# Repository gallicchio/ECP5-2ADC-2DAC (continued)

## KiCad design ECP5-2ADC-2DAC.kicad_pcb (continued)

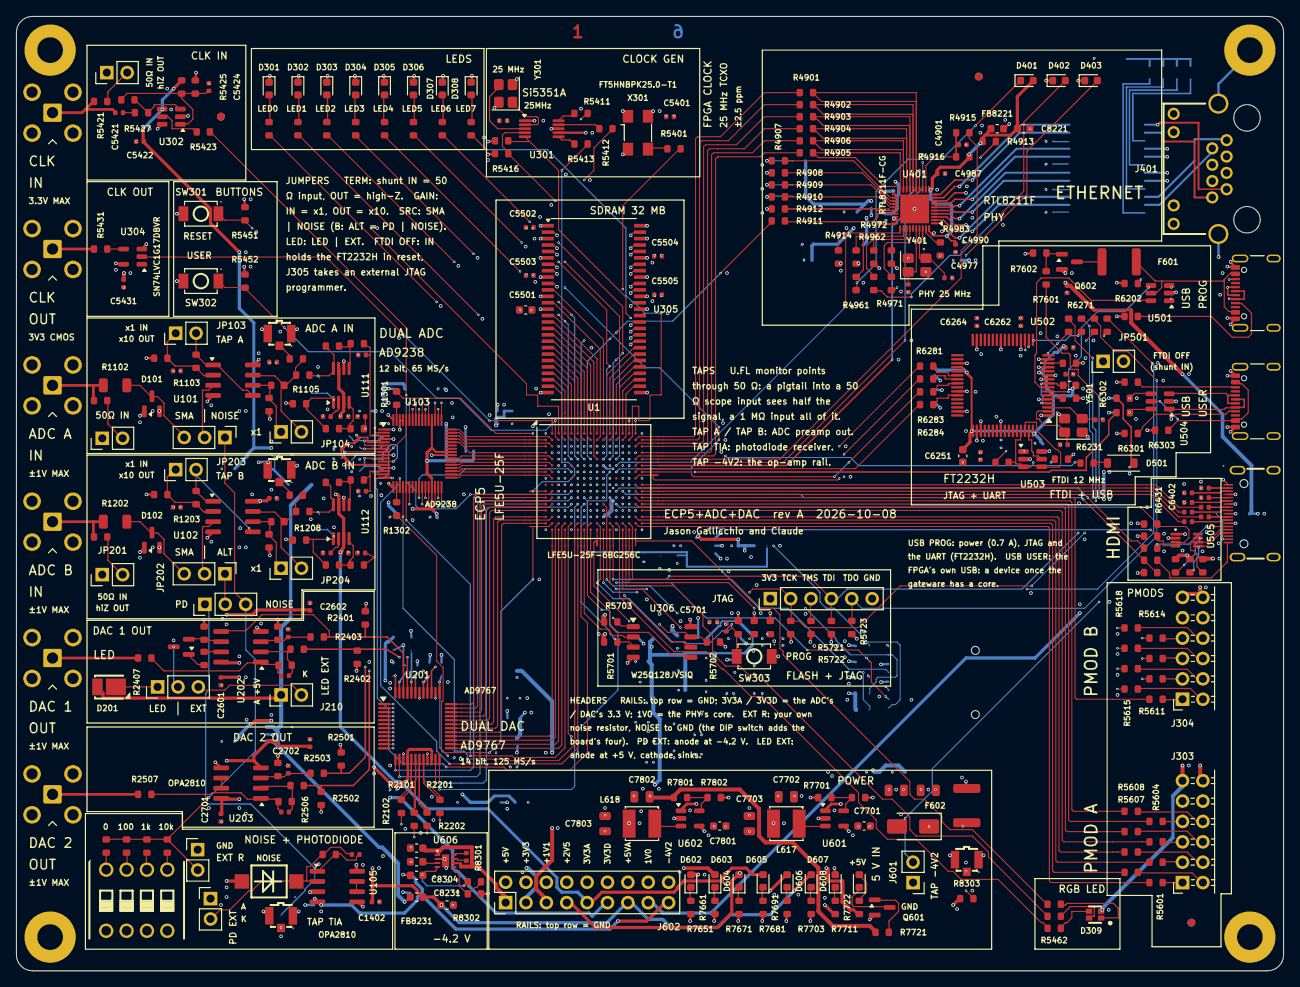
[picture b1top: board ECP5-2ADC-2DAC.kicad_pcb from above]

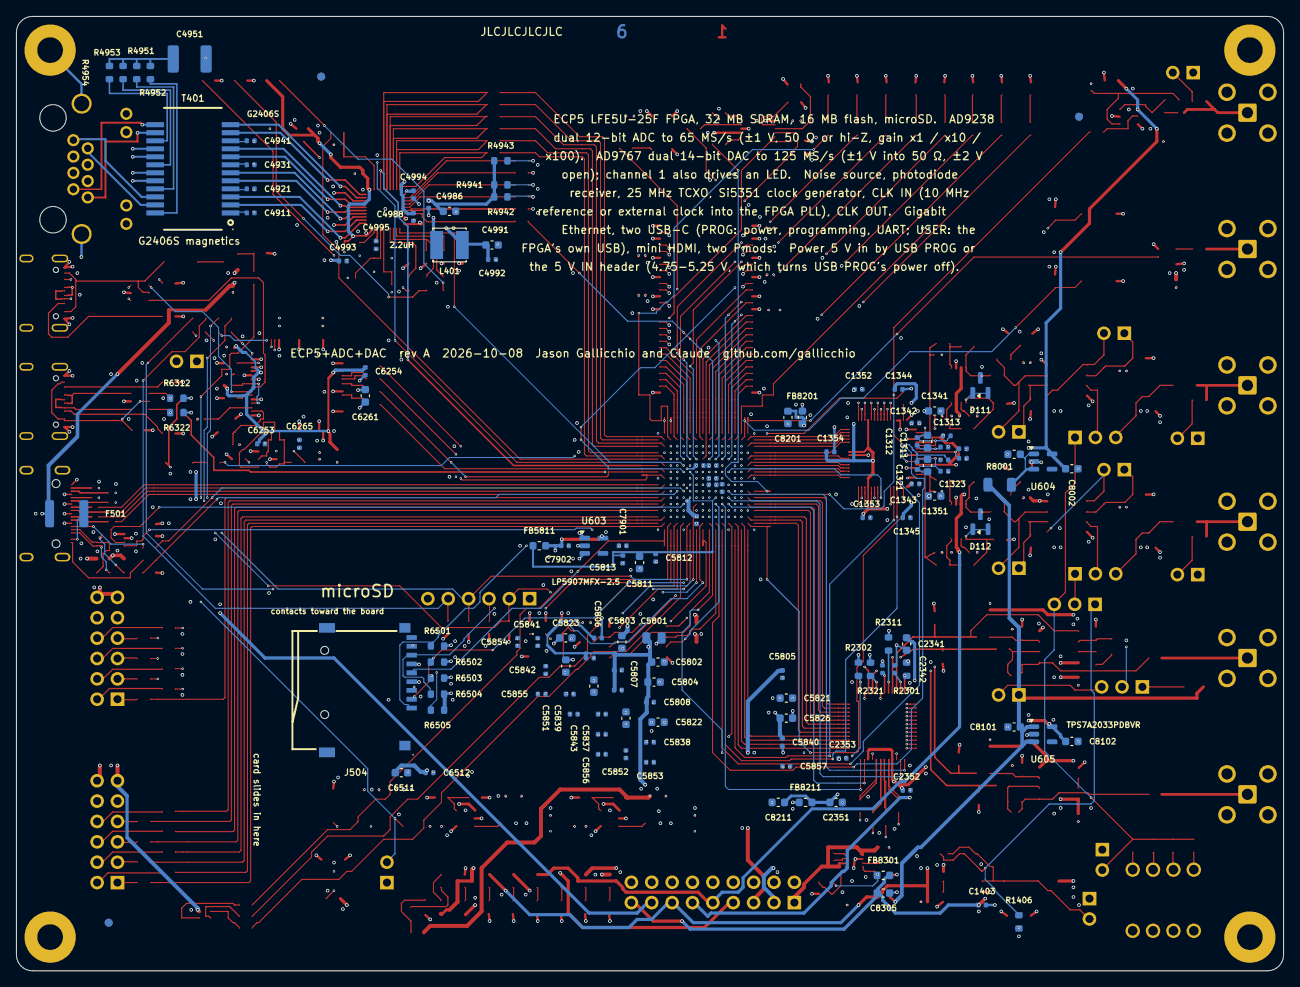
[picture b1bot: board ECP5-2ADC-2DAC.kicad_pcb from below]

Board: 6 copper layers, 158.0 x 119.0 mm, 478 parts (127 on the bottom side), 446 nets.

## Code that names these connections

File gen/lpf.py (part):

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         '_io = [',
         '    # Clocks: 25 MHz TCXO is the default; the Si5351 outputs and the external SMA are also PCLK inputs',
         '    ("clk25",   0, Pins("%s"), IOStandard("LVCMOS33")),' % a["CLK_TCXO"],
         '    ("clk_ext", 0, Pins("%s"), IOStandard("LVCMOS33")),' % a["CLK_EXT"],
         '    ("clk_si",  0, Pins("%s"), IOStandard("LVCMOS33")),' % a["CLK_SI0"],
         '    ("clk_si",  1, Pins("%s"), IOStandard("LVCMOS33")),' % a["CLK_SI1"],
         '    ("clk_si",  2, Pins("%s"), IOStandard("LVCMOS33")),' % a["CLK_SI2"],
         '    ("clk_out", 0, Pins("%s"), IOStandard("LVCMOS33")),' % a["CLK_OUT"],
         '    ("rst",     0, Pins("%s"), IOStandard("LVCMOS33"), Misc("PULLMODE=UP")),' % a["BTN0"],
         '    ("user_btn", 0, Pins("%s"), IOStandard("LVCMOS33"), Misc("PULLMODE=UP")),' % a["BTN0"],
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        L.append('    ("user_led", %d, Pins("%s"), IOStandard("LVCMOS33")),' % (i, a["LED%d" % i]))
    L += ['    # Serial: FT2232H channel B',
          '    ("serial", 0,',
          '        Subsignal("tx", Pins("%s")),' % a["UART_TX"],
          '        Subsignal("rx", Pins("%s")),' % a["UART_RX"],
          '        IOStandard("LVCMOS33")',
          '    ),',
          '    # SDR SDRAM: W9825G6KH-6, 32 MB',
          '    ("sdram_clock", 0, Pins("%s"), IOStandard("LVCMOS33")),' % a["SDRAM_CLK"],
          '    ("sdram", 0,',
          '        Subsignal("a",     Pins("%s")),' % P(["SDRAM_A%d" % i for i in range(13)]),
          '        Subsignal("dq",    Pins("%s")),' % P(["SDRAM_DQ%d" % i for i in range(16)]),
          '        Subsignal("we_n",  Pins("%s")),' % a["SDRAM_WE_N"],
          '        Subsignal("ras_n", Pins("%s")),' % a["SDRAM_RAS_N"],
          '        Subsignal("cas_n", Pins("%s")),' % a["SDRAM_CAS_N"],
          '        Subsignal("cs_n",  Pins("%s")),' % a["SDRAM_CS_N"],
          '        Subsignal("cke",   Pins("%s")),' % a["SDRAM_CKE"],
          '        Subsignal("ba",    Pins("%s")),' % P(["SDRAM_BA0", "SDRAM_BA1"]),
          '        Subsignal("dm",    Pins("%s")),' % P(["SDRAM_DQML", "SDRAM_DQMH"]),
          '        IOStandard("LVCMOS33"), Misc("SLEWRATE=SLOW"),      # unterminated 8-31 mm lines at 100 MHz: slow edges are the termination',
          '    ),',
          '    # SPI flash: W25Q128JVS on the sysCONFIG pins (CLK = CCLK, driven through USRMCLK)',
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          '    ),',
          '    # microSD',
          '    ("spisdcard", 0,',
          '        Subsignal("clk",  Pins("%s")),' % a["SD_CLK"],
          '        Subsignal("mosi", Pins("%s"), Misc("PULLMODE=UP")),' % a["SD_CMD"],
          '        Subsignal("cs_n", Pins("%s"), Misc("PULLMODE=UP")),' % a["SD_D3"],
          '        Subsignal("miso", Pins("%s"), Misc("PULLMODE=UP")),' % a["SD_D0"],
          '        Misc("SLEWRATE=FAST"), IOStandard("LVCMOS33"),',
          '    ),',
          '    ("sdcard", 0,',
          '        Subsignal("clk",  Pins("%s")),' % a["SD_CLK"],
          '        Subsignal("cmd",  Pins("%s"), Misc("PULLMODE=UP")),' % a["SD_CMD"],
          '        Subsignal("data", Pins("%s"), Misc("PULLMODE=UP")),' % P(["SD_D0", "SD_D1", "SD_D2", "SD_D3"]),
          '        Misc("SLEWRATE=FAST"), IOStandard("LVCMOS33"),',
          '    ),',
          '    # Gigabit Ethernet: RTL8211F-CG, RGMII at 3.3 V',
          '    ("eth_clocks", 0,',
          '        Subsignal("tx", Pins("%s")),' % a["ETH_TXC"],
          '        Subsignal("rx", Pins("%s")),' % a["ETH_RXC"],
          '        IOStandard("LVCMOS33")',
          '    ),',
          '    ("eth", 0,',
          '        Subsignal("rst_n",   Pins("%s")),' % a["ETH_RST_N"],
          '        Subsignal("int_n",   Pins("%s")),' % a["ETH_INT_N"],
          '        Subsignal("mdio",    Pins("%s")),' % a["ETH_MDIO"],
          '        Subsignal("mdc",     Pins("%s")),' % a["ETH_MDC"],
          '        Subsignal("rx_ctl",  Pins("%s")),' % a["ETH_RX_CTL"],
          '        Subsignal("rx_data", Pins("%s")),' % P(["ETH_RXD%d" % i for i in range(4)]),
          '        Subsignal("tx_ctl",  Pins("%s")),' % a["ETH_TX_CTL"],
          '        Subsignal("tx_data", Pins("%s")),' % P(["ETH_TXD%d" % i for i in range(4)]),
          '        IOStandard("LVCMOS33")',
          '    ),',
          '    # Direct USB (ULX3S style): D+/D- through 27R, 1k5-ish pull-up on D+ switched by the FPGA',
          '    ("usb", 0,',
          '        Subsignal("d_p",    Pins("%s")),' % a["USB_DP"],
          '        Subsignal("d_n",    Pins("%s")),' % a["USB_DN"],
          '        Subsignal("pullup", Pins("%s")),' % a["USB_PULLUP"],
          '        IOStandard("LVCMOS33")',
          '    ),',
          '    # GPDI (HDMI), 22 nF AC coupled pairs, emulated differential',
          '    ("gpdi", 0,',
          '        Subsignal("clk_p",   Pins("%s"), IOStandard("LVCMOS33D"), Misc("DRIVE=4")),' % a["GPDI_CK_P"],
          '        Subsignal("data0_p", Pins("%s"), IOStandard("LVCMOS33D"), Misc("DRIVE=4")),' % a["GPDI_D0_P"],
          '        Subsignal("data1_p", Pins("%s"), IOStandard("LVCMOS33D"), Misc("DRIVE=4")),' % a["GPDI_D1_P"],
          '        Subsignal("data2_p", Pins("%s"), IOStandard("LVCMOS33D"), Misc("DRIVE=4")),' % a["GPDI_D2_P"],
          '        Subsignal("hpd", Pins("%s"), IOStandard("LVCMOS33"), Misc("PULLMODE=UP")),' % a["GPDI_HPD"],
          '        Subsignal("cec", Pins("%s"), IOStandard("LVCMOS33"), Misc("PULLMODE=UP")),' % a["GPDI_CEC"],
          '        Subsignal("scl", Pins("%s"), IOStandard("LVCMOS33"), Misc("PULLMODE=UP")),' % a["GPDI_SCL"],
          '        Subsignal("sda", Pins("%s"), IOStandard("LVCMOS33"), Misc("PULLMODE=UP")),' % a["GPDI_SDA"],
          '    ),',
          '    # Si5351A clock generator, I2C',
          '    ("i2c", 0,',
          '        Subsignal("scl", Pins("%s")),' % a["I2C_SCL"],
          '        Subsignal("sda", Pins("%s")),' % a["I2C_SDA"],
          '        IOStandard("LVCMOS33"), Misc("PULLMODE=UP"),',
          '    ),',
          '    # AD9238 dual 12-bit ADC: two parallel ports, FPGA drives both sample clocks',
          '    ("adc", 0,',
          '        Subsignal("clk_a",  Pins("%s")),' % a["ADC_A_CLK"],
          '        Subsignal("clk_b",  Pins("%s")),' % a["ADC_B_CLK"],
          '        Subsignal("d_a",    Pins("%s")),' % P(["ADC_A_D%d" % i for i in range(12)]),
          '        Subsignal("d_b",    Pins("%s")),' % P(["ADC_B_D%d" % i for i in range(12)]),
          '        Subsignal("otr_a",  Pins("%s")),' % a["ADC_A_OTR"],
          '        Subsignal("otr_b",  Pins("%s")),' % a["ADC_B_OTR"],
          '        Subsignal("dcs",    Pins("%s")),' % a["ADC_DCS"],
          '        Subsignal("dfs",    Pins("%s")),' % a["ADC_DFS"],
          '        Subsignal("pdwn_a", Pins("%s")),' % a["ADC_PDWN_A"],
          '        Subsignal("pdwn_b", Pins("%s")),' % a["ADC_PDWN_B"],
          '        IOStandard("LVCMOS33")',
          '    ),',
          '    # AD9767 dual 14-bit DAC: two parallel ports with their own CLK and WRT',
          '    ("dac", 0,',
          '        Subsignal("d1",    Pins("%s")),' % P(["DAC_P1_D%d" % i for i in range(14)]),
          '        Subsignal("d2",    Pins("%s")),' % P(["DAC_P2_D%d" % i for i in range(14)]),
          '        Subsignal("clk1",  Pins("%s"), Misc("SLEWRATE=FAST")),' % a["DAC_CLK1"],
          '        Subsignal("clk2",  Pins("%s"), Misc("SLEWRATE=FAST")),' % a["DAC_CLK2"],
          '        Subsignal("wrt1",  Pins("%s"), Misc("SLEWRATE=FAST")),' % a["DAC_WRT1"],
          '        Subsignal("wrt2",  Pins("%s"), Misc("SLEWRATE=FAST")),' % a["DAC_WRT2"],
          '        Subsignal("mode",  Pins("%s")),' % a["DAC_MODE"],
          '        Subsignal("sleep", Pins("%s")),' % a["DAC_SLEEP"],
          '        IOStandard("LVCMOS33"), Misc("SLEWRATE=SLOW"),      # the 37-58 mm data lines: slow; the clocks and WRTs (33 R at the DAC) fast',
          '    ),',
          '    # FT2232H channel B modem lines, usable as a reset/boot select from the PC',
          '    ("ftdi_rts", 0, Pins("%s"), IOStandard("LVCMOS33")),' % a["FTDI_RTS"],
          '    ("ftdi_dtr", 0, Pins("%s"), IOStandard("LVCMOS33")),' % a["FTDI_DTR"],
          ']', '',
          '_connectors = [',
          '    ("PMODA", "%s"),' % P(["PMODA_%d" % i for i in range(8)]),
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
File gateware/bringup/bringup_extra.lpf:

# Pin settings for the bring-up design only, appended to the generated ../ecp5_2adc_2dac.lpf by build.sh (a later
# IOBUF line for a port replaces the earlier one's settings).  The generated file is the board's; these are choices
# of this one design.
# USB USER: no pull inside the FPGA.  The generated file pulls D+ and D- up, which against a host's 15 k to ground
# would hold both lines near mid-rail; the only pull-up a device port wants is the board's 1.5 k on usb_pullup.
IOBUF PORT "usb_dp" IO_TYPE=LVCMOS33 PULLMODE=NONE;
IOBUF PORT "usb_dn" IO_TYPE=LVCMOS33 PULLMODE=NONE;
# microSD: the data lines pulled up, so an empty socket reads all ones and a card's open-drain start is clean.
IOBUF PORT "sd_d[0]" IO_TYPE=LVCMOS33 PULLMODE=UP;
IOBUF PORT "sd_d[1]" IO_TYPE=LVCMOS33 PULLMODE=UP;
IOBUF PORT "sd_d[2]" IO_TYPE=LVCMOS33 PULLMODE=UP;
# HDMI: hot-plug detect reads 0 with no monitor; the DDC lines idle high.
IOBUF PORT "gpdi_hpd" IO_TYPE=LVCMOS33 PULLMODE=DOWN;
IOBUF PORT "gpdi_scl" IO_TYPE=LVCMOS33 PULLMODE=UP;
IOBUF PORT "gpdi_sda" IO_TYPE=LVCMOS33 PULLMODE=UP;
# Pmods: pulled down, so an unplugged pin reads 0 and the loop test's "nothing wired" is a definite answer.
IOBUF PORT "pmoda[0]" IO_TYPE=LVCMOS33 PULLMODE=DOWN;
IOBUF PORT "pmoda[1]" IO_TYPE=LVCMOS33 PULLMODE=DOWN;
IOBUF PORT "pmoda[2]" IO_TYPE=LVCMOS33 PULLMODE=DOWN;
IOBUF PORT "pmoda[3]" IO_TYPE=LVCMOS33 PULLMODE=DOWN;
IOBUF PORT "pmoda[4]" IO_TYPE=LVCMOS33 PULLMODE=DOWN;
IOBUF PORT "pmoda[5]" IO_TYPE=LVCMOS33 PULLMODE=DOWN;
IOBUF PORT "pmoda[6]" IO_TYPE=LVCMOS33 PULLMODE=DOWN;
IOBUF PORT "pmoda[7]" IO_TYPE=LVCMOS33 PULLMODE=DOWN;
IOBUF PORT "pmodb[0]" IO_TYPE=LVCMOS33 PULLMODE=DOWN;
IOBUF PORT "pmodb[1]" IO_TYPE=LVCMOS33 PULLMODE=DOWN;
IOBUF PORT "pmodb[2]" IO_TYPE=LVCMOS33 PULLMODE=DOWN;
IOBUF PORT "pmodb[3]" IO_TYPE=LVCMOS33 PULLMODE=DOWN;
IOBUF PORT "pmodb[4]" IO_TYPE=LVCMOS33 PULLMODE=DOWN;
IOBUF PORT "pmodb[5]" IO_TYPE=LVCMOS33 PULLMODE=DOWN;
IOBUF PORT "pmodb[6]" IO_TYPE=LVCMOS33 PULLMODE=DOWN;
IOBUF PORT "pmodb[7]" IO_TYPE=LVCMOS33 PULLMODE=DOWN;
# HDMI data and clock pins: 4 mA, as the board's LiteX platform file and the demo design set them (the generated LPF
# gives no DRIVE, and the tools' default is 8 mA).  Each pair is two single-ended pins driven in antiphase through 22 nF.
IOBUF PORT "gpdi_d0_p" IO_TYPE=LVCMOS33 DRIVE=4;
IOBUF PORT "gpdi_d0_n" IO_TYPE=LVCMOS33 DRIVE=4;
IOBUF PORT "gpdi_d1_p" IO_TYPE=LVCMOS33 DRIVE=4;
IOBUF PORT "gpdi_d1_n" IO_TYPE=LVCMOS33 DRIVE=4;
IOBUF PORT "gpdi_d2_p" IO_TYPE=LVCMOS33 DRIVE=4;
IOBUF PORT "gpdi_d2_n" IO_TYPE=LVCMOS33 DRIVE=4;
IOBUF PORT "gpdi_ck_p" IO_TYPE=LVCMOS33 DRIVE=4;
IOBUF PORT "gpdi_ck_n" IO_TYPE=LVCMOS33 DRIVE=4;
# RGMII transmit pins: fast edges.  The generated LPF and the LiteX platform file give them no SLEWRATE (the tools'
# default is SLOW); at gigabit a bit is 4 ns.  This is a bring-up choice to be judged by the loopback's error count
# (bench.py v1b, eth_loop): if frames come back bad, build once with these six lines removed and compare.
IOBUF PORT "eth_txc" IO_TYPE=LVCMOS33 SLEWRATE=FAST;
IOBUF PORT "eth_tx_ctl" IO_TYPE=LVCMOS33 SLEWRATE=FAST;
IOBUF PORT "eth_txd[0]" IO_TYPE=LVCMOS33 SLEWRATE=FAST;
IOBUF PORT "eth_txd[1]" IO_TYPE=LVCMOS33 SLEWRATE=FAST;
IOBUF PORT "eth_txd[2]" IO_TYPE=LVCMOS33 SLEWRATE=FAST;
IOBUF PORT "eth_txd[3]" IO_TYPE=LVCMOS33 SLEWRATE=FAST;

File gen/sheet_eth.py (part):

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    # management: hierarchical labels at one x, pull-ups above each wire
    mdc, mdio, intb, rst = ph.pin("13"), ph.pin("14"), ph.pin("31"), ph.pin("12")
    xh = mdc[0] - 27.94
    s.wire(*mdc, xh, mdc[1]); s.hlabel(xh, mdc[1], "ETH_MDC", shape="input", rot=180)
    s.wire(*mdio, xh, mdio[1]); s.hlabel(xh, mdio[1], "ETH_MDIO", shape="bidirectional", rot=180)
    pullup(ctx, 900, mdio[0] - 20.32, mdio[1], "4.7k", "+3V3_ETH")       # (clear of the chip's dashed box since 2026-10-07)
    s.wire(*intb, xh, intb[1]); s.hlabel(xh, intb[1], "ETH_INT_N", shape="output", rot=180)
    pullup(ctx, 900, intb[0] - 20.32, intb[1], "4.7k", "+3V3_ETH")
    rr = R(ctx, 900, "330R", rst[0] - 19.05, rst[1], horiz=True, ref_at=(rst[0] - 21.6, rst[1] - 1.6), val_at=(rst[0] - 21.6, rst[1] + 1.3))
    s.wire(*rr.pin(2), *rst); s.wire(*rr.pin(1), xh, rst[1]); s.hlabel(xh, rst[1], "ETH_RST_N", shape="input", rot=180)
    pullup(ctx, 900, rst[0] - 10.16, rst[1], "4.7k", "+3V3_ETH")
    cr = C(ctx, 900, "1uF", rst[0] - 3.81, rst[1] + 6.35, side="right"); s.junction(rst[0] - 3.81, rst[1])
    s.wire(rst[0] - 3.81, rst[1], *cr.pin(1)); gnd(ctx, *cr.pin(2), stub=1.27)
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        s.wire(*r1.pin(2), *a1); gnd(ctx, *k1, stub=2.54)
        rp = R(ctx, base, "4.7k", xr, lp[1] + 5.08, side="right"); s.wire(xr, lp[1], *rp.pin(1)); gnd(ctx, *rp.pin(2), stub=2.54)
    label_node(ctx, xl - 91.7, l1[1] + 9.5, "LED1: 100M link (active high); strap CFG_LDO0 = 0", side="right", size=0.85)
    label_node(ctx, xl - 107.7, l2[1] + 23.0, "LED2: 1000M link (active high); strap CFG_LDO1 = 0", side="right", size=0.85)
    # crystal on XTAL_IN/OUT: jogs of 2.54 to the crystal's 7.62 mm pin pitch
    xi, xo, clko = ln.pin("36"), ln.pin("37"), ln.pin("35")
    # four pads: 1 and 3 are the crystal, 2 and 4 the grounded case (the YXC drawing)
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    label_node(ctx, rs[0] + 19.0, rs[1] + 0.5, "line driver current reference, 1 %", side="right", size=0.85)
    # the TXDLY strap (build 26): RXD1 pulled up through 4.7 k to DVDD_RG, so the PHY adds the 2 ns transmit delay as
    # well as the receive one -- both RGMII delays inside the PHY ("rgmii-id"), the gateware adds none (reviews, R5)
    s.label(330.0, 300.0, "ETH_RXD1", size=0.8)                                    # (the bus member's own name since build 28: one name per net)
    s.wire(330.0, 300.0, 340.36, 300.0)
    pullup(ctx, 940, 340.36, 300.0, "4.7k", "+3V3_ETH")
    label_node(ctx, 330.0, 304.0, "RXD1 strap: TXDLY = 1 (4.7 k to DVDD_RG)", side="right", size=0.85)
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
